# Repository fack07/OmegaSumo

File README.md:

# 🤖 Robô Lutador de Sumô Autônomo de 3 kg

Este repositório contém o projeto **Omega Sumo**, um robô autônomo de sumô de 3 kg, desenvolvido como parte do **Trabalho de Conclusão de Curso (TCC)** em Engenharia de Computação da UTFPR – Campus Pato Branco.

O projeto aborda a **atualização de hardware e software** do robô, com foco na implementação de um **sistema supervisório baseado em SED (Sistemas a Eventos Discretos)**, visando estratégias eficientes e melhoria de desempenho em combate.

---

## ⚙️ Estrutura do Repositório

| Pasta | Descrição |
|-------|------------|
| [`Firmware/`](./Firmware) | Contém o código embarcado para o microcontrolador STM32F407VET6, implementando controle de sensores, motores e o supervisor em tempo real. |
| [`Supervisor/`](./Supervisor) | Contém o modelo supervisório desenvolvido no Supremica (`omega_sumo.wmod`), compactado em `.zip`, reunindo as plantas, especificações e supervisor. |
| [`PCB/`](./PCB) | Projeto eletrônico do robô, incluindo esquemáticos e layout da placa. |

---
## 🧰 Ferramentas Utilizadas
- [Supremica](https://www.supremica.org) – Modelagem e síntese supervisória (uso acadêmico)  
- [STM32CubeIDE](https://www.st.com/en/development-tools/stm32cubeide.html) – Desenvolvimento e compilação do firmware  
- [Autodesk EAGLE](https://www.autodesk.com/products/eagle/overview) – Desenvolvimento do projeto eletrônico e layout de PCB  
- [GitHub](https://github.com/) – Controle de versão e compartilhamento do projeto  

---

## 📜 Licença e Uso
Este projeto foi desenvolvido para fins **acadêmicos e de pesquisa**.  
Os arquivos gerados pelo Supremica são distribuídos conforme sua licença de uso educativo.  
O código-fonte embarcado e o projeto eletrônico podem ser reutilizados livremente para fins não comerciais, com a devida citação do autor.

---

## 👤 Autor

**Fabio Kinukawa**  
Engenharia de Computação — UTFPR

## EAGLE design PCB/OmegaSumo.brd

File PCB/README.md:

# ⚡ Projeto Eletrônico – Omega Sumo (PCB)

Esta pasta contém o **projeto eletrônico** do robô autônomo de sumô **Omega Sumo**, desenvolvido no contexto do Trabalho de Conclusão de Curso (TCC) em Engenharia de Computação da UTFPR – Câmpus Pato Branco.

O circuito foi projetado no **Autodesk EAGLE 9.x**, abrangendo os módulos de potência, controle e sensores do robô.  
O objetivo do projeto é fornecer uma base estável e modular para o sistema embarcado do robô, compatível com o microcontrolador **STM32F407VET6**.

---

## 🧩 Estrutura dos Arquivos

| Arquivo | Descrição |
|-----------------|------------|
| `OmegaSumo.sch` | Esquemático principal do circuito eletrônico, contendo o microcontrolador, drivers de motor, sensores e interfaces de comunicação. |
| `OmegaSumo.brd` | Layout da placa de circuito impresso (PCB), desenvolvido a partir do esquemático. |
| `pcb_top.png` | Imagens 2D e/ou 3D da placa geradas no EAGLE. |
| `pcb_bottom.png` | Imagens 2D e/ou 3D da placa geradas no EAGLE. |
| `OmegaSumo_PCB.zip` | Arquivo compactado contendo todos os arquivos nativos do projeto EAGLE. |

---

## ⚙️ Especificações Técnicas

- **Software:** Autodesk EAGLE 9.x  
- **Camadas:** 2 (dupla face)  
- **Dimensões aproximadas:** conforme layout (otimizado para o chassi do robô Omega Sumo)  
- **Alimentação:** 7,4 V (Li-Po 2S)  
- **Tensão lógica:** 3,3 V  
- **Controlador principal:** STM32F407VET6  
- **Interfaces principais:** sensores IR, sensores de linha, drivers de motor, botão de start, LEDs de status  

---

## 🛠️ Como Abrir o Projeto

1. Instale o **Autodesk EAGLE** (versão 9.x ou superior).  
2. Baixe e extraia o arquivo [`OmegaSumo_PCB.zip`](./OmegaSumo_PCB.zip).  
3. Abra o arquivo `OmegaSumo.sch` no EAGLE.  
4. Verifique o esquemático e sincronize com o layout (`OmegaSumo.brd`) caso necessário.  
5. Gere os arquivos Gerber para fabricação em **File → CAM Processor → Generate Gerbers**.

---

## ⚠️ Boas Práticas de Projeto

- Mantenha trilhas de potência largas (≥ 1 mm para corrente de motor).  
- Utilize planos de terra (`GND Plane`) para reduzir ruído e interferência.  
- Separe áreas de potência e lógica no layout.  
- Verifique a orientação de componentes polarizados (diodos, capacitores eletrolíticos, conectores).  
- Sempre execute o **DRC (Design Rule Check)** antes da geração dos Gerbers.

---

## 📜 Licença

Este projeto é distribuído para **fins acadêmicos e de pesquisa**, sendo permitido seu uso como referência em estudos e trabalhos relacionados a sistemas embarcados e robótica móvel.  
É proibido o uso comercial sem autorização do autor.

---

## ✍️ Autor

**Fabio Kinukawa**  
Trabalho de Conclusão de Curso – Engenharia de Computação  
UTFPR – Universidade Tecnológica Federal do Paraná  
Equipe: **PatoBots**

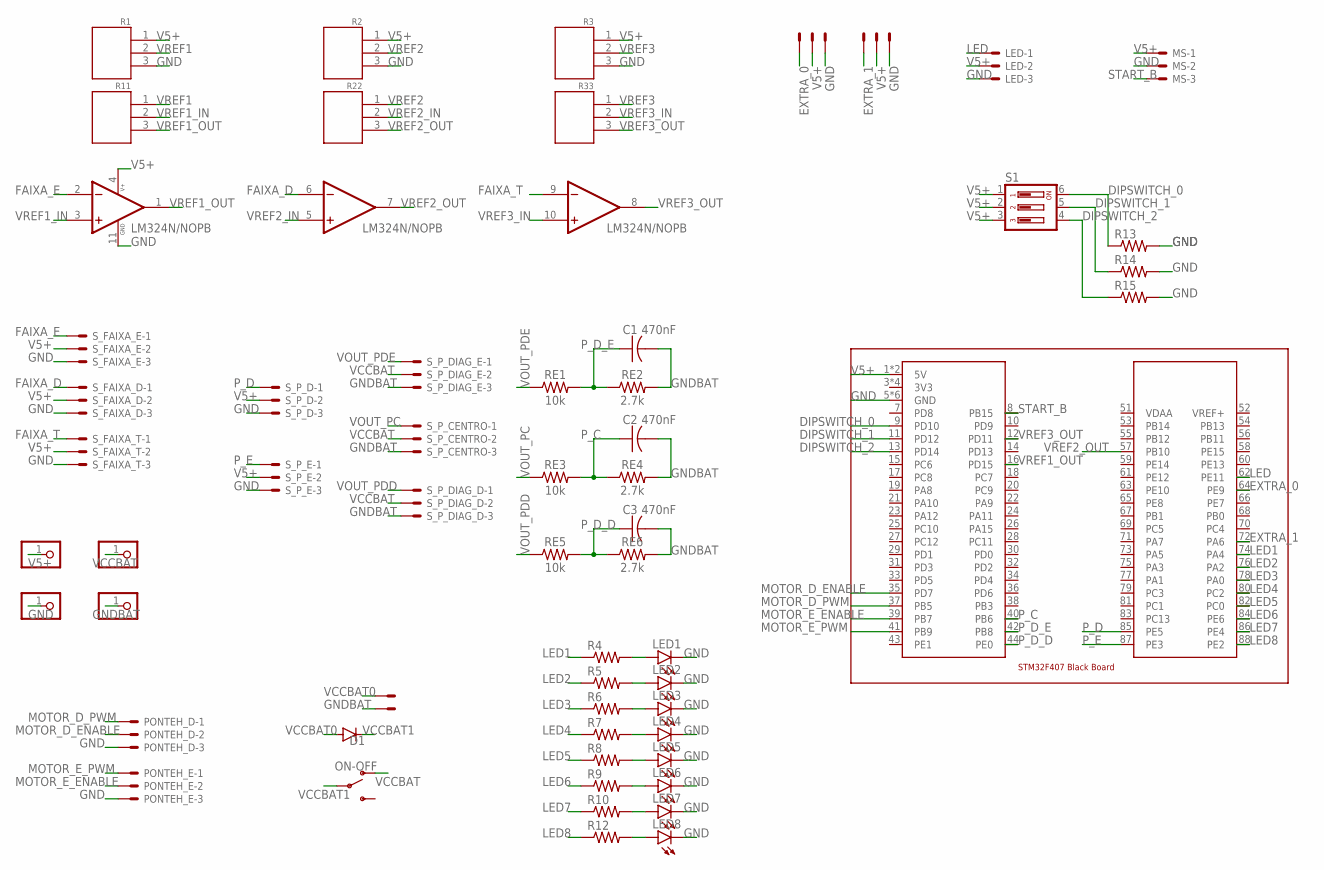
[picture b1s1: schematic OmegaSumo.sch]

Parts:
5V: PINHD-1X1; 1X01
BAT: 22-23-2021
C1, C2, C3: 470nF; C050-025X075
D1: 1N4148DO35-7; DO35-7
EXTRA, EXTRA1: 22-23-2031
GNDBAT: PINHD-1X1; 1X01
GNDOUT: PINHD-1X1; 1X01
LED: 22-23-2031
LED1, LED2, LED3, LED4, LED5, LED6, LED7, LED8: LED3MM
MS: 22-23-2031
ON-OFF: SWITCH-SPDT-PTH-8.6X4.3MM-LOCK; SWITCH_SPDT_8.6X4.3MM_LOCK
PONTEH_D: 22-23-2031
PONTEH_E: 22-23-2031
R1, R2, R3, R11, R22, R33: RM065
R4, R5, R6, R7, R8, R9, R10, R12, R13, R14, R15: R-US_0204/7; 0204/7
RE1, RE3, RE5: 10k; 0204/7
RE2, RE4, RE6: 2.7k; 0204/7
S1: DIP03YL
S_FAIXA_D: 22-23-2031
S_FAIXA_E: 22-23-2031
S_FAIXA_T: 22-23-2031
S_P_CENTRO: 22-23-2031
S_P_D: 22-23-2031
S_P_DIAG_D: 22-23-2031
S_P_DIAG_E: 22-23-2031
S_P_E: 22-23-2031
U$5: LM324N/NOPB; DIP825W47P254L1917H533Q14
U$6: LIB1BLACK_BOARD; STM32F407
VCCBAT: PINHD-1X1; 1X01

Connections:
DIPSWITCH_0: R13.1, S1.6, U$6.9 (PD10)
DIPSWITCH_1: R14.1, S1.5, U$6.11 (PD12)
DIPSWITCH_2: R15.1, S1.4, U$6.13 (PD14)
EXTRA_0: EXTRA.1, U$6.64 (PE9)
EXTRA_1: EXTRA1.1, U$6.72 (PA6)
FAIXA_D: S_FAIXA_D.1, U$5.6 (2IN-)
FAIXA_E: S_FAIXA_E.1, U$5.2 (1IN-)
FAIXA_T: S_FAIXA_T.1, U$5.9 (3IN-)
GND: EXTRA.3, EXTRA1.3, GNDOUT.1, LED.3, LED1.K (C), LED2.K (C), LED3.K (C), LED4.K (C), LED5.K (C), LED6.K (C), LED7.K (C), LED8.K (C), MS.2, PONTEH_D.3, PONTEH_E.3, R1.3, R2.3, R3.3, R13.2, R14.2, R15.2, S_FAIXA_D.3, S_FAIXA_E.3, S_FAIXA_T.3, S_P_D.3, S_P_E.3, U$5.11 (GND), U$6.5 (GND), U$6.6 (GND), U$6.47 (GND), U$6.48 (GND), U$6.49 (GND), U$6.50 (GND)
GNDBAT: BAT.2, C1.2, C2.2, C3.2, GNDBAT.1, RE2.2, RE4.2, RE6.2, S_P_CENTRO.3, S_P_DIAG_D.3, S_P_DIAG_E.3
LED: LED.1, U$6.62 (PE11)
LED1: R4.1, U$6.74 (PA4)
LED2: R5.1, U$6.76 (PA2)
LED3: R6.1, U$6.78 (PA0)
LED4: R7.1, U$6.80 (PC2)
LED5: R8.1, U$6.82 (PC0)
LED6: R9.1, U$6.84 (PE6)
LED7: R10.1, U$6.86 (PE4)
LED8: R12.1, U$6.88 (PE2)
MOTOR_D_ENABLE: PONTEH_D.2, U$6.35 (PD7)
MOTOR_D_PWM: PONTEH_D.1, U$6.37 (PB5)
MOTOR_E_ENABLE: PONTEH_E.2, U$6.39 (PB7)
MOTOR_E_PWM: PONTEH_E.1, U$6.41 (PB9)
unnamed: LED1.A, R4.2
unnamed: LED2.A, R5.2
unnamed: LED3.A, R6.2
unnamed: LED4.A, R7.2
unnamed: LED5.A, R8.2
unnamed: LED6.A, R9.2
unnamed: LED7.A, R10.2
unnamed: LED8.A, R12.2
P_C: C2.1, RE3.2, RE4.1, U$6.40 (PB6)
P_D: S_P_D.1, U$6.85 (PE5)
P_D_D: C3.1, RE5.2, RE6.1, U$6.44 (PE0)
P_D_E: C1.1, RE1.2, RE2.1, U$6.42 (PB8)
P_E: S_P_E.1, U$6.87 (PE3)
START_B: MS.3, U$6.8 (PB15)
V5+: 5V.1, EXTRA.2, EXTRA1.2, LED.2, MS.1, R1.1, R2.1, R3.1, S1.1, S1.2, S1.3, S_FAIXA_D.2, S_FAIXA_E.2, S_FAIXA_T.2, S_P_D.2, S_P_E.2, U$5.4 (V+), U$6.1 (5V), U$6.2 (5V)
VCCBAT: ON-OFF.1 (O), S_P_CENTRO.2, S_P_DIAG_D.2, S_P_DIAG_E.2, VCCBAT.1
VCCBAT0: BAT.1, D1.A
VCCBAT1: D1.C, ON-OFF.2
VOUT_PC: RE3.1, S_P_CENTRO.1
VOUT_PDD: RE5.1, S_P_DIAG_D.1
VOUT_PDE: RE1.1, S_P_DIAG_E.1
VREF1: R1.2, R11.1
VREF1_IN: R11.2, U$5.3 (1IN+)
VREF1_OUT: R11.3, U$5.1 (1OUT), U$6.16 (PD15)
VREF2: R2.2, R22.1
VREF2_IN: R22.2, U$5.5 (2IN+)
VREF2_OUT: R22.3, U$5.7 (2OUT), U$6.57 (PB10)
VREF3: R3.2, R33.1
VREF3_IN: R33.2, U$5.10 (3IN+)
VREF3_OUT: R33.3, U$5.8 (3OUT), U$6.12 (PD11)

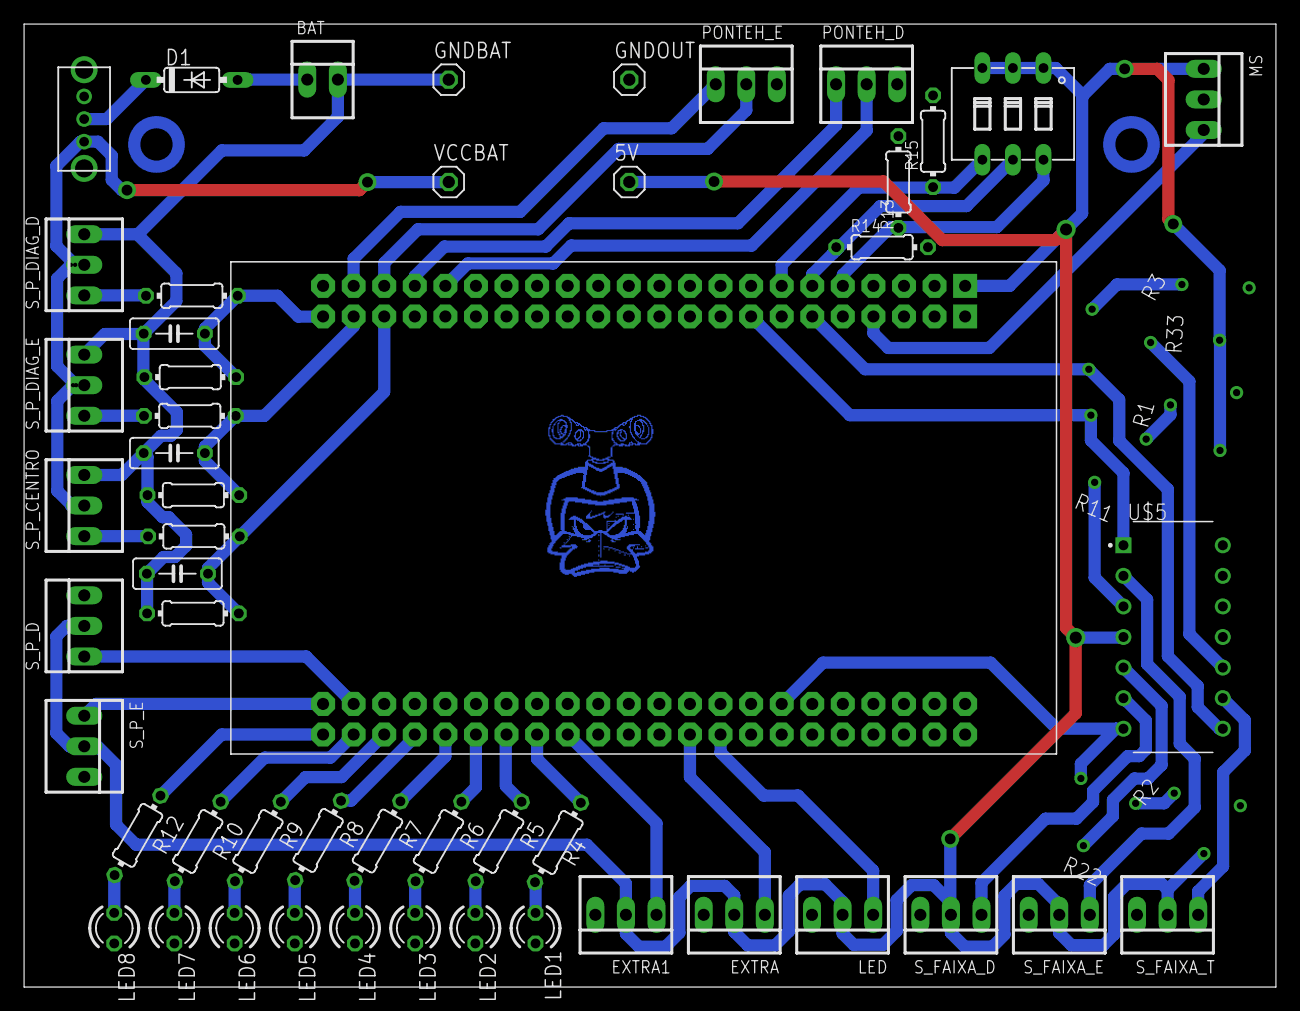
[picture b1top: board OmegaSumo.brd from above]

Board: 2 copper layers, 104.0 x 80.0 mm, 58 parts (0 on the bottom side), 53 nets.

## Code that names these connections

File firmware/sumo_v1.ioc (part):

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Mcu.Name=STM32F407V(E-G)Tx
Mcu.Package=LQFP100
Mcu.UserName=STM32F407VETx
PA0-WKUP.GPIOParameters=GPIO_Label
PA0-WKUP.GPIO_Label=LED6
PA0-WKUP.Signal=GPIO_Output
PA2.GPIOParameters=GPIO_Label
PA2.GPIO_Label=LED7
PA2.Signal=GPIO_Output
PA4.GPIOParameters=GPIO_Label
PA4.GPIO_Label=LED8
PA4.Signal=GPIO_Output
PA6.GPIOParameters=GPIO_Label
PA6.GPIO_Label=BANDEIRA
PA6.Signal=GPIO_Output
PB10.GPIOParameters=GPIO_Label,GPIO_ModeDefaultEXTI
PB10.GPIO_Label=FAIXA2
PB10.GPIO_ModeDefaultEXTI=GPIO_MODE_IT_RISING
PB10.Signal=GPXTI10
PB15.GPIOParameters=GPIO_Label
PB15.GPIO_Label=MICROSTART
PB15.Signal=GPIO_Input
PB5.GPIOParameters=GPIO_Label
PB5.GPIO_Label=MOTOR_E_ENABLE
PB5.Signal=GPIO_Output
PB6.GPIOParameters=GPIO_Label,GPIO_ModeDefaultEXTI
PB6.GPIO_Label=PRESENCA3
PB6.GPIO_ModeDefaultEXTI=GPIO_MODE_IT_RISING_FALLING
PB6.Signal=GPXTI6
PB7.Signal=S_TIM4_CH2
PB8.GPIOParameters=GPIO_Label,GPIO_ModeDefaultEXTI
PB8.GPIO_Label=PRESENCA2
PB8.GPIO_ModeDefaultEXTI=GPIO_MODE_IT_RISING_FALLING
PB8.Signal=GPXTI8
PB9.Signal=S_TIM11_CH1
PC0.GPIOParameters=GPIO_Label
PC0.GPIO_Label=LED4
PC0.Signal=GPIO_Output
PC2.GPIOParameters=GPIO_Label
PC2.GPIO_Label=LED5
PC2.Signal=GPIO_Output
PD10.GPIOParameters=GPIO_PuPd,GPIO_Label
PD10.GPIO_Label=DIPS0
PD10.GPIO_PuPd=GPIO_PULLDOWN
PD10.Signal=GPIO_Input
PD11.GPIOParameters=GPIO_Label,GPIO_ModeDefaultEXTI
PD11.GPIO_Label=FAIXA3
PD11.GPIO_ModeDefaultEXTI=GPIO_MODE_IT_RISING
PD11.Signal=GPXTI11
PD12.GPIOParameters=GPIO_PuPd,GPIO_Label
PD12.GPIO_Label=DIPS1
PD12.GPIO_PuPd=GPIO_PULLDOWN
PD12.Signal=GPIO_Input
PD14.GPIOParameters=GPIO_PuPd,GPIO_Label
PD14.GPIO_Label=DIPS2
PD14.GPIO_PuPd=GPIO_PULLDOWN
PD14.Signal=GPIO_Input
PD15.GPIOParameters=GPIO_Label,GPIO_ModeDefaultEXTI
PD15.GPIO_Label=FAIXA1
PD15.GPIO_ModeDefaultEXTI=GPIO_MODE_IT_RISING
PD15.Signal=GPXTI15
PD7.GPIOParameters=GPIO_Label
PD7.GPIO_Label=MOTOR_D_ENABLE
PD7.Signal=GPIO_Output
PE0.GPIOParameters=GPIO_Label,GPIO_ModeDefaultEXTI
PE0.GPIO_Label=PRESENCA4
PE0.GPIO_ModeDefaultEXTI=GPIO_MODE_IT_RISING_FALLING
PE0.Signal=GPXTI0
PE2.GPIOParameters=GPIO_Label
PE2.GPIO_Label=LED1
PE2.Signal=GPIO_Output
PE3.GPIOParameters=GPIO_Label
PE3.GPIO_Label=PRESENCA5
PE3.Signal=GPXTI3
PE4.GPIOParameters=GPIO_Label
PE4.GPIO_Label=LED2
PE4.Signal=GPIO_Output
PE5.GPIOParameters=GPIO_Label
PE5.GPIO_Label=PRESENCA1
PE5.Signal=GPXTI5
PE6.GPIOParameters=GPIO_Label
PE6.GPIO_Label=LED3
PE6.Signal=GPIO_Output
PH0-OSC_IN.Mode=HSE-External-Oscillator
PH0-OSC_IN.Signal=RCC_OSC_IN
PH1-OSC_OUT.Mode=HSE-External-Oscillator
PH1-OSC_OUT.Signal=RCC_OSC_OUT
RCC.HSE_VALUE=8000000
RCC.SYSCLKFreq_VALUE=168000000
RCC.SYSCLKSource=RCC_SYSCLKSOURCE_PLLCLK
board=custom

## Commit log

2025-11-10 Rename sumo_modular - automato.wmod to omega_sumo.wmod

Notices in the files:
parts and their libraries:
SparkFun-Switches: Licensing: Creative Commons ShareAlike 4.0 International - https://creativecommons.org/licenses/by-sa/4.0
